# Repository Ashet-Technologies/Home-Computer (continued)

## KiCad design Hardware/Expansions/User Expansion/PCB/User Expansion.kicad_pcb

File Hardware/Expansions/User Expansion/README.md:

# User Expansion

This expansion card allows one to create their own expansions.

It contains all necessary parts like the connector and the metadata EEPROM, but apart from that, it just exposes all signals onto a perfboard.

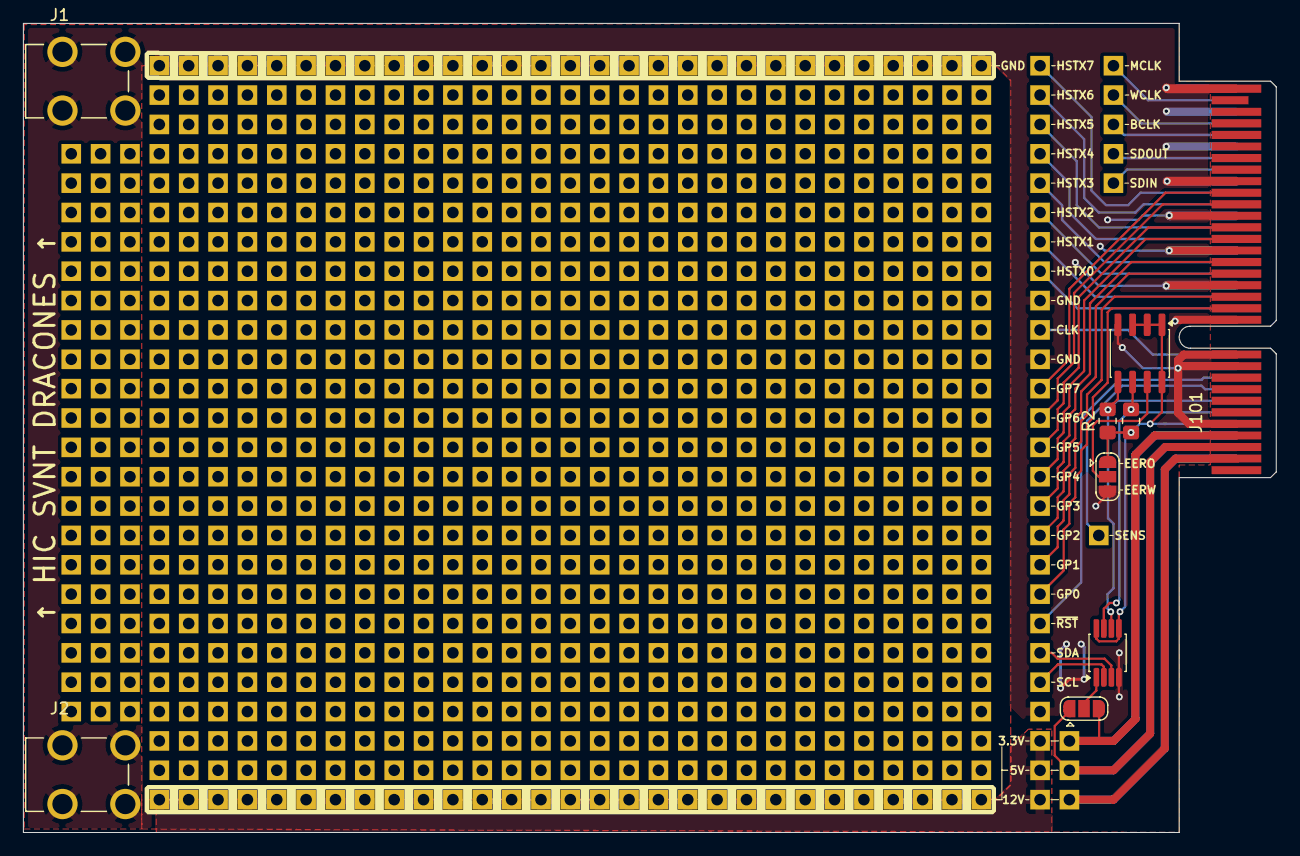
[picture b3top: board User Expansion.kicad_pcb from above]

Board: 2 copper layers, 108.4 x 70.0 mm, 102 parts (0 on the bottom side), 36 nets.

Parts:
J1, J2: 7774; KEYSTONE_7774
J101: BUS_PCIexpress_x4
JP101, JP102: WP; SolderJumper-3_P1.3mm_Open_RoundedPad1.0x1.5mm
R1, R2: 10K; R_0805_2012Metric_Pad1.20x1.40mm_HandSolder
TP101, TP104, TP105, TP106, TP107, TP108, TP109, TP110, TP111, TP112, TP113, TP114, TP115, TP116, TP117, TP118, TP119, TP120, TP121, TP122, TP123, TP124, TP125, TP126, TP127, TP132, TP133, TP135, TP136, TP137, TP138, TP139, TP140, TP141, TP142: Perfboard_Pad_P2.54mm
TP1301, TP1302, TP1303, TP1304, TP1305, TP1306, TP1307, TP1308, TP1309, TP1310, TP1311, TP1312, TP1313, TP1314, TP1315, TP1316, TP1317, TP1318, TP1319, TP1320, TP1321, TP1322, TP1323, TP1324, TP1325, TP1326, TP1327, TP1328, TP1329, TP1401, TP1402, TP1403, TP1404, TP1405, TP1406, TP1407, TP1408, TP1409, TP1410, TP1411, TP1412, TP1413, TP1414, TP1415, TP1416, TP1417, TP1418, TP1419, TP1420, TP1421, TP1422, TP1423, TP1425, TP1426, TP1427, TP1429, TP1430, TP1431: -; Perfboard_Pad_P2.54mm
U1: 24LC256; SOIC-8_3.9x4.9mm_P1.27mm
U2: TCA9517ADGKR; VSSOP-8_3x3mm_P0.65mm

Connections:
+3.3VP: J101.A5 (+3V3_ID), JP101.1 (A), R1.1, R2.1, U1.1 (A0), U1.2 (A1), U1.3 (A2), U1.8 (VCC), U2.5 (EN), U2.8 (VCC_{B})
+3V3: J101.A4 (+3V3), J101.B4 (+3V3), JP102.3 (B), TP141.1 (1_1)
+5V: J101.A3 (+5V), J101.B3 (+5V), JP102.1 (A), TP139.1 (1_1)
+12V: J101.A2 (+12V), J101.B2 (+12V), TP140.1 (1_1)
/CLK: J101.A11 (CLK), TP106.1 (1_1)
/Connected Row1/COM: TP135.1 (1_1), TP137.1 (1_1), TP138.1 (1_1), TP1401.1 (1_1), TP1402.1 (1_1), TP1403.1 (1_1), TP1404.1 (1_1), TP1405.1 (1_1), TP1406.1 (1_1), TP1407.1 (1_1), TP1408.1 (1_1), TP1409.1 (1_1), TP1410.1 (1_1), TP1411.1 (1_1), TP1412.1 (1_1), TP1413.1 (1_1), TP1414.1 (1_1), TP1415.1 (1_1), TP1416.1 (1_1), TP1417.1 (1_1), TP1418.1 (1_1), TP1419.1 (1_1), TP1420.1 (1_1), TP1421.1 (1_1), TP1422.1 (1_1), TP1423.1 (1_1), TP1425.1 (1_1), TP1426.1 (1_1), TP1427.1 (1_1), TP1429.1 (1_1), TP1430.1 (1_1), TP1431.1 (1_1)
/GP0: J101.B13 (GP0), TP115.1 (1_1)
/GP1: J101.B14 (GP1), TP116.1 (1_1)
/GP2: J101.B16 (GP2), TP117.1 (1_1)
/GP3: J101.B17 (GP3), TP118.1 (1_1)
/GP4: J101.B19 (GP4), TP119.1 (1_1)
/GP5: J101.B20 (GP5), TP120.1 (1_1)
/GP6: J101.B22 (GP6), TP121.1 (1_1)
/GP7: J101.B23 (GP7), TP122.1 (1_1)
/HSTX0: J101.A13 (HSTX0), TP107.1 (1_1)
/HSTX1: J101.A14 (HSTX1), TP108.1 (1_1)
/HSTX2: J101.A16 (HSTX2), TP109.1 (1_1)
/HSTX3: J101.A17 (HSTX3), TP110.1 (1_1)
/HSTX4: J101.A19 (HSTX4), TP111.1 (1_1)
/HSTX5: J101.A20 (HSTX5), TP112.1 (1_1)
/HSTX6: J101.A22 (HSTX6), TP113.1 (1_1)
/HSTX7: J101.A23 (HSTX7), TP114.1 (1_1)
/I2S_BCLK: J101.A28 (I2S_BCLK), TP125.1 (1_1)
/I2S_MCLK: J101.A31 (I2S_MCLK), TP127.1 (1_1)
/I2S_SDIN: J101.A25 (I2S_SDIN), TP123.1 (1_1)
/I2S_SDOUT: J101.A26 (I2S_SDOUT), TP124.1 (1_1)
/I2S_WCLK: J101.A29 (I2S_WCLK), TP126.1 (1_1)
/MOD_SENS: J101.A8 (+3V3_10K), TP104.1 (1_1)
/SCL: TP132.1 (1_1), U2.2 (SCL_{A})
/SCL_{ID}: J101.A6 (I2C_SCL), R1.2, U1.6 (SCL), U2.7 (SCL_{B})
/SDA: TP142.1 (1_1), U2.3 (SDA_{A})
/SDA_{ID}: J101.A7 (I2C_SDA), R2.2, U1.5 (SDA), U2.6 (SDA_{B})
/~RESET: J101.A9 (~RESET), TP105.1 (1_1)
GND: J1.1_1, J1.1_2, J1.1_3, J1.1_4, J2.1_1, J2.1_2, J2.1_3, J2.1_4, J101.A10 (GND), J101.A12 (GND), J101.A15 (GND), J101.A18 (GND), J101.A21 (GND), J101.A24 (GND), J101.A27 (GND), J101.A30 (GND), J101.A32 (GND), J101.B5 (GND), J101.B10 (~PRESENT), J101.B11 (GND), J101.B12 (GND), J101.B15 (GND), J101.B18 (GND), J101.B21 (GND), J101.B24 (GND), J101.B32 (GND), JP101.3 (B), TP101.1 (1_1), TP133.1 (1_1), TP136.1 (1_1), TP1301.1 (1_1), TP1302.1 (1_1), TP1303.1 (1_1), TP1304.1 (1_1), TP1305.1 (1_1), TP1306.1 (1_1), TP1307.1 (1_1), TP1308.1 (1_1), TP1309.1 (1_1), TP1310.1 (1_1), TP1311.1 (1_1), TP1312.1 (1_1), TP1313.1 (1_1), TP1314.1 (1_1), TP1315.1 (1_1), TP1316.1 (1_1), TP1317.1 (1_1), TP1318.1 (1_1), TP1319.1 (1_1), TP1320.1 (1_1), TP1321.1 (1_1), TP1322.1 (1_1), TP1323.1 (1_1), TP1324.1 (1_1), TP1325.1 (1_1), TP1326.1 (1_1), TP1327.1 (1_1), TP1328.1 (1_1), TP1329.1 (1_1), U1.4 (GND), U2.4 (GND)
unnamed: JP101.2 (C), U1.7 (WP)
unnamed: JP102.2 (C), U2.1 (VCC_{A})

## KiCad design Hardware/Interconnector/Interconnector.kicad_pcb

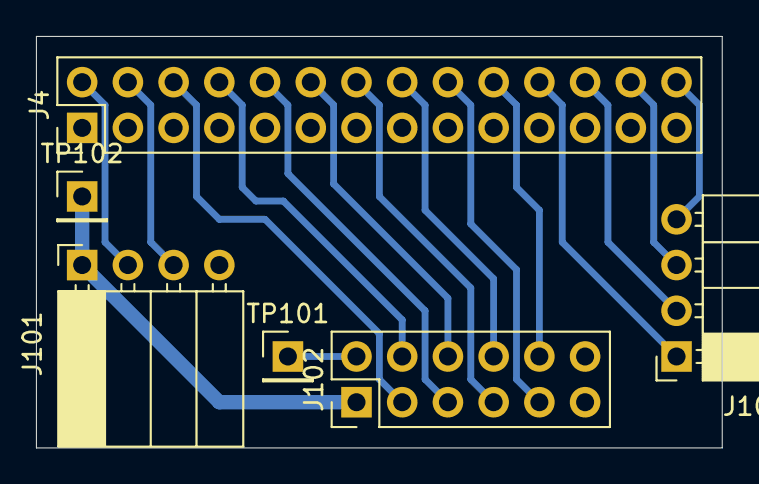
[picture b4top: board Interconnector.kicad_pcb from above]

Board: 2 copper layers, 38.1 x 22.9 mm, 6 parts (0 on the bottom side), 17 nets.

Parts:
J4: Conn_Center; PinHeader_2x14_P2.54mm_Vertical
J101, J103: Conn_01x04; PinSocket_1x04_P2.54mm_Horizontal
J102: Conn_02x06_Odd_Even; PinHeader_2x06_P2.54mm_Vertical
TP101, TP102: TestPoint; PinHeader_1x01_P2.54mm_Vertical

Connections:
+3.3V: J101.1, J102.1, TP102.1
/GPIO22: J4.2, J101.2
/GPIO23: J4.4, J101.3
/GPIO24: J4.6, J102.3
/GPIO25: J4.8, J102.4
/GPIO26: J4.10, J102.5
/GPIO27: J4.12, J102.6
/GPIO28: J4.14, J102.7
/GPIO29: J4.16, J102.8
/GPIO30: J4.18, J102.9
/GPIO31: J4.20, J102.10
/GPIO32: J4.22, J103.1
/GPIO33: J4.24, J103.2
/GPIO34: J4.26, J103.3
/GPIO35: J4.28, J103.4
/~P2_RES: J102.2, TP101.1
GND: J4.1, J4.3, J4.5, J4.7, J4.9, J4.11, J4.13, J4.15, J4.17, J4.19, J4.21, J4.23, J4.25, J4.27, J101.4, J102.11, J102.12

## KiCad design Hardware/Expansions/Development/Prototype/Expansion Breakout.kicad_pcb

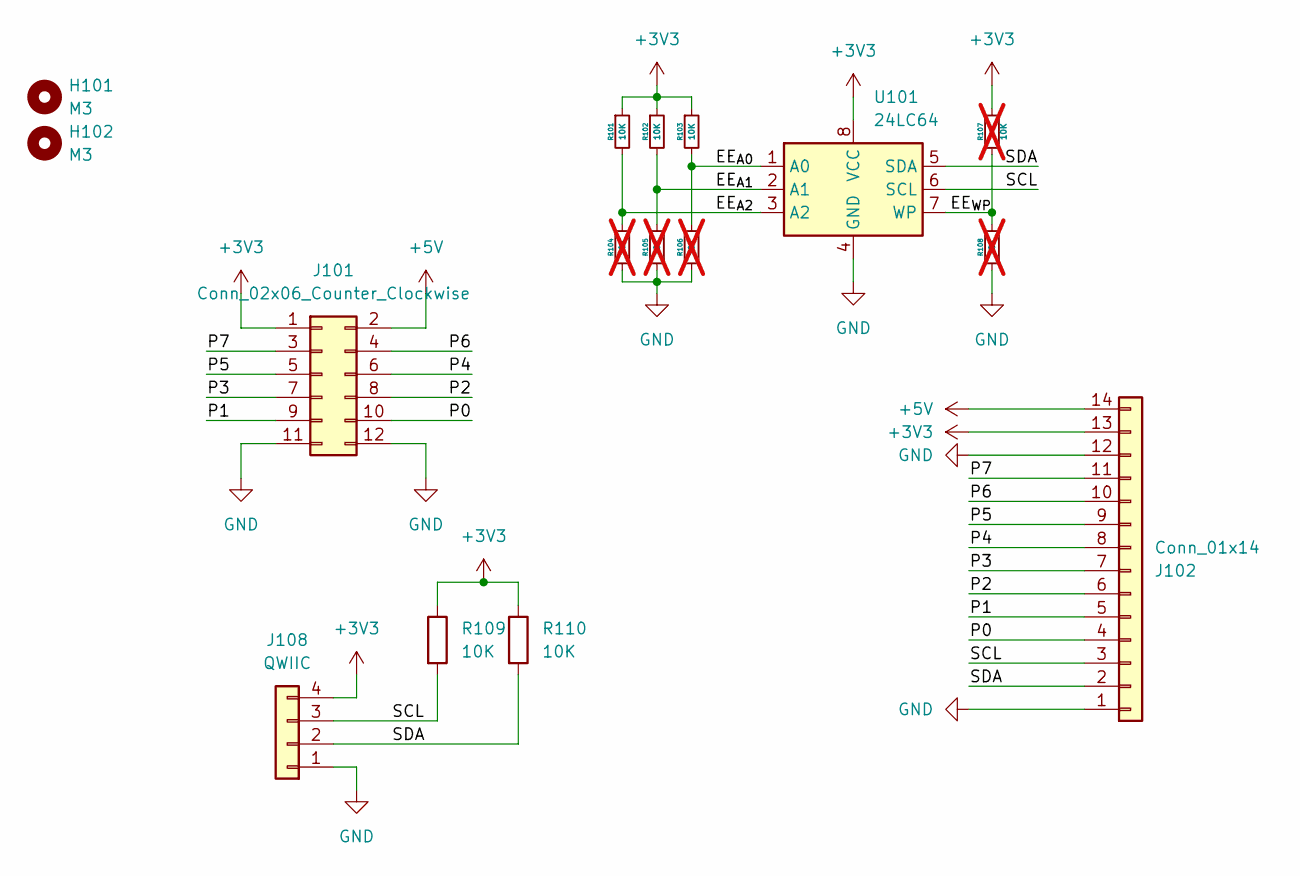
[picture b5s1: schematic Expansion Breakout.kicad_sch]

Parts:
H101, H102: M3; MountingHole_3.2mm_M3_ISO7380
J101: Conn_02x06_Counter_Clockwise; PinHeader_2x06_P2.54mm_Vertical
J102: Conn_01x14; PinSocket_1x14_P2.54mm_Horizontal
J108: QWIIC; PinSocket_1x04_P2.54mm_Horizontal
R101, R102, R103: 10K; R_0603_1608Metric_Pad0.98x0.95mm_HandSolder
R104, R105, R106, R107, R108: 10K; R_0603_1608Metric_Pad0.98x0.95mm_HandSolder; not fitted
R109, R110: 10K; R_Axial_DIN0207_L6.3mm_D2.5mm_P10.16mm_Horizontal
U101: 24LC64; DIP-8_W7.62mm_LongPads

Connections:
+3V3: J101.1, J102.13, J108.4, R101.1, R102.1, R103.1, R107.1, R109.1, R110.1, U101.8 (VCC)
+5V: J101.2, J102.14
/EE_{A0}: R103.2, R106.1, U101.1 (A0)
/EE_{A1}: R102.2, R105.1, U101.2 (A1)
/EE_{A2}: R101.2, R104.1, U101.3 (A2)
/EE_{WP}: R107.2, R108.1, U101.7 (WP)
/P0: J101.10, J102.4
/P1: J101.9, J102.5
/P2: J101.8, J102.6
/P3: J101.7, J102.7
/P4: J101.6, J102.8
/P5: J101.5, J102.9
/P6: J101.4, J102.10
/P7: J101.3, J102.11
/SCL: J102.3, J108.3, R109.2, U101.6 (SCL)
/SDA: J102.2, J108.2, R110.2, U101.5 (SDA)
GND: J101.11, J101.12, J102.1, J102.12, J108.1, R104.2, R105.2, R106.2, R108.2, U101.4 (GND)

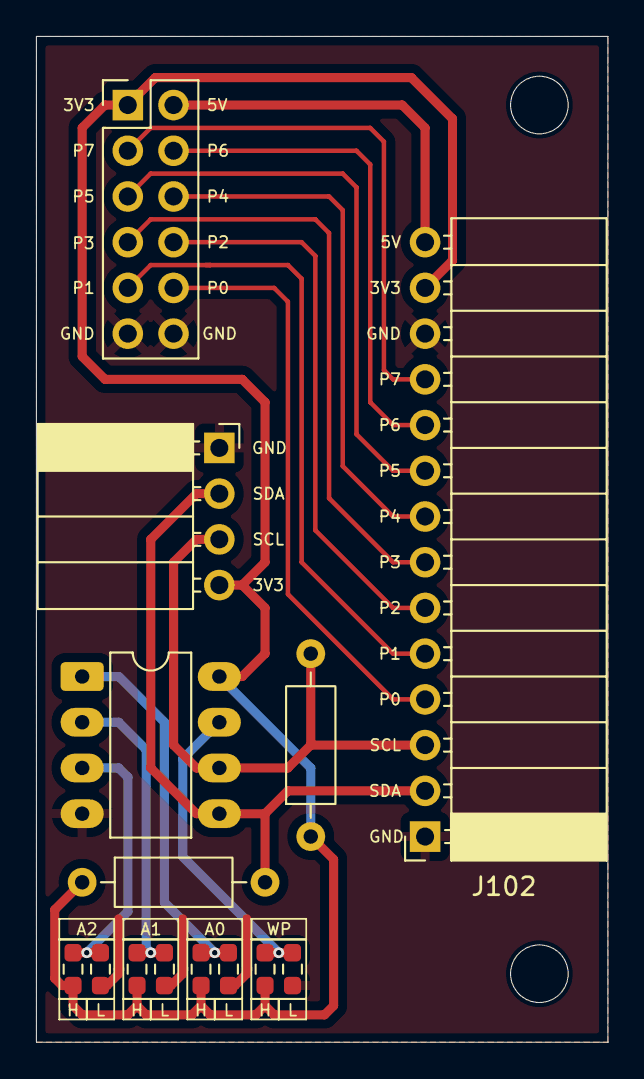
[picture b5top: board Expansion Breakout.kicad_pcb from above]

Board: 2 copper layers, 31.8 x 55.9 mm, 16 parts (0 on the bottom side), 17 nets.

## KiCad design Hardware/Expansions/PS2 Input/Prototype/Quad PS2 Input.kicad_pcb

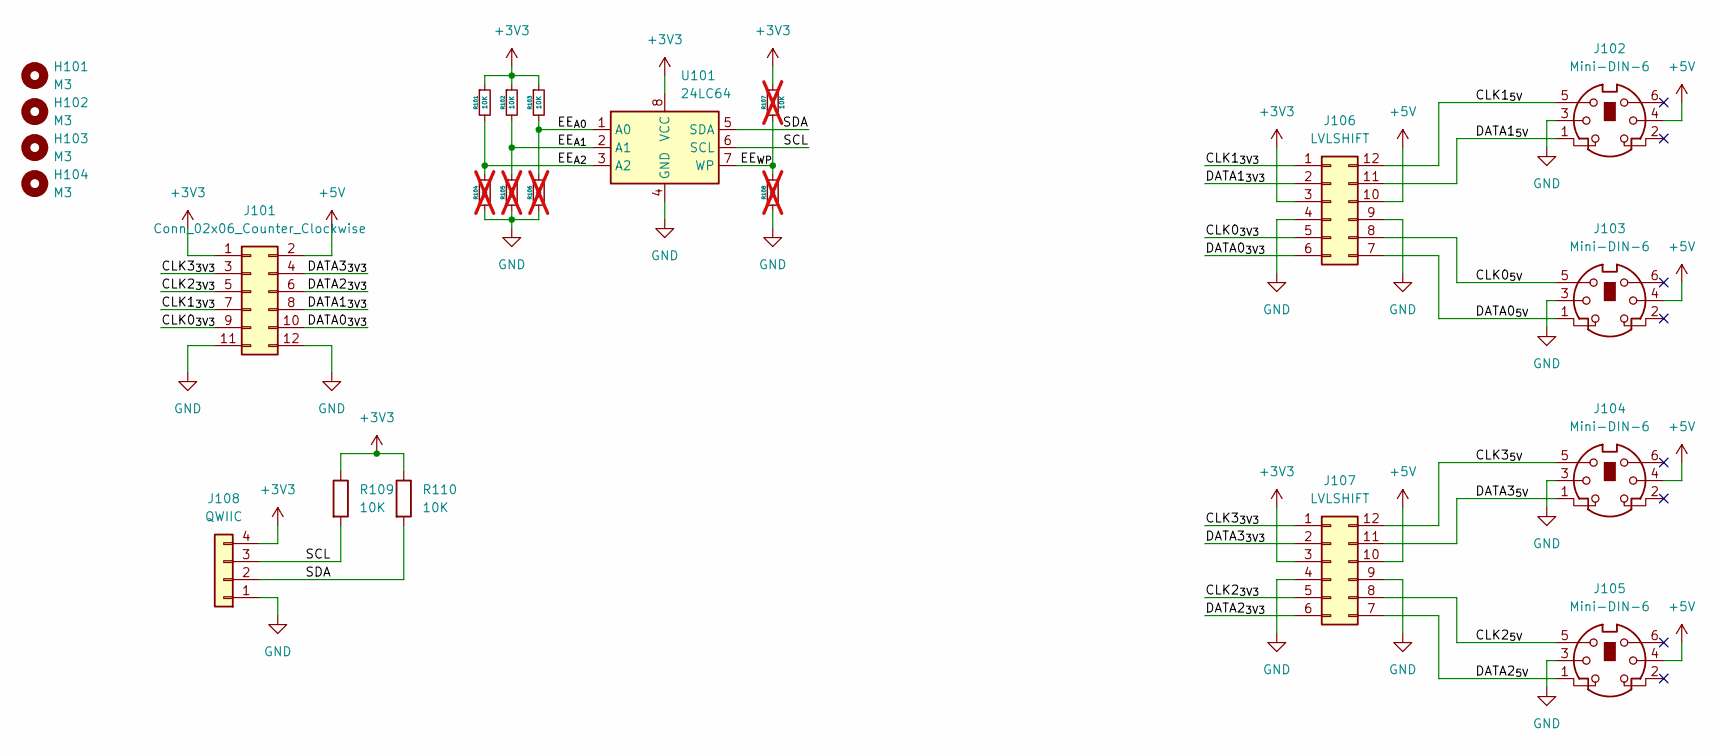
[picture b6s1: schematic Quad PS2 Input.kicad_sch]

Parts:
H101, H102, H103, H104: M3; MountingHole_3.2mm_M3_ISO7380
J101: Conn_02x06_Counter_Clockwise; PinHeader_2x06_P2.54mm_Vertical
J102, J103, J104, J105: Mini-DIN-6; J_Mini-DIN-6
J106, J107: LVLSHIFT; DIP-12_W10.16mm
J108: QWIIC; PinSocket_1x04_P2.54mm_Horizontal
R101, R102, R103: 10K; R_0603_1608Metric_Pad0.98x0.95mm_HandSolder
R104, R105, R106, R107, R108: 10K; R_0603_1608Metric_Pad0.98x0.95mm_HandSolder; not fitted
R109, R110: 10K; R_Axial_DIN0207_L6.3mm_D2.5mm_P10.16mm_Horizontal
U101: 24LC64; DIP-8_W7.62mm_LongPads

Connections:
+3V3: J101.1, J106.3, J107.3, J108.4, R101.1, R102.1, R103.1, R107.1, R109.1, R110.1, U101.8 (VCC)
+5V: J101.2, J102.4, J103.4, J104.4, J105.4, J106.10, J107.10
/CLK0_{3V3}: J101.9, J106.5
/CLK0_{5V}: J103.5, J106.8
/CLK1_{3V3}: J101.7, J106.1
/CLK1_{5V}: J102.5, J106.12
/CLK2_{3V3}: J101.5, J107.5
/CLK2_{5V}: J105.5, J107.8
/CLK3_{3V3}: J101.3, J107.1
/CLK3_{5V}: J104.5, J107.12
/DATA0_{3V3}: J101.10, J106.6
/DATA0_{5V}: J103.1, J106.7
/DATA1_{3V3}: J101.8, J106.2
/DATA1_{5V}: J102.1, J106.11
/DATA2_{3V3}: J101.6, J107.6
/DATA2_{5V}: J105.1, J107.7
/DATA3_{3V3}: J101.4, J107.2
/DATA3_{5V}: J104.1, J107.11
/EE_{A0}: R103.2, R106.1, U101.1 (A0)
/EE_{A1}: R102.2, R105.1, U101.2 (A1)
/EE_{A2}: R101.2, R104.1, U101.3 (A2)
/EE_{WP}: R107.2, R108.1, U101.7 (WP)
/SCL: J108.3, R109.2, U101.6 (SCL)
/SDA: J108.2, R110.2, U101.5 (SDA)
GND: J101.11, J101.12, J102.3, J103.3, J104.3, J105.3, J106.4, J106.9, J107.4, J107.9, J108.1, R104.2, R105.2, R106.2, R108.2, U101.4 (GND)

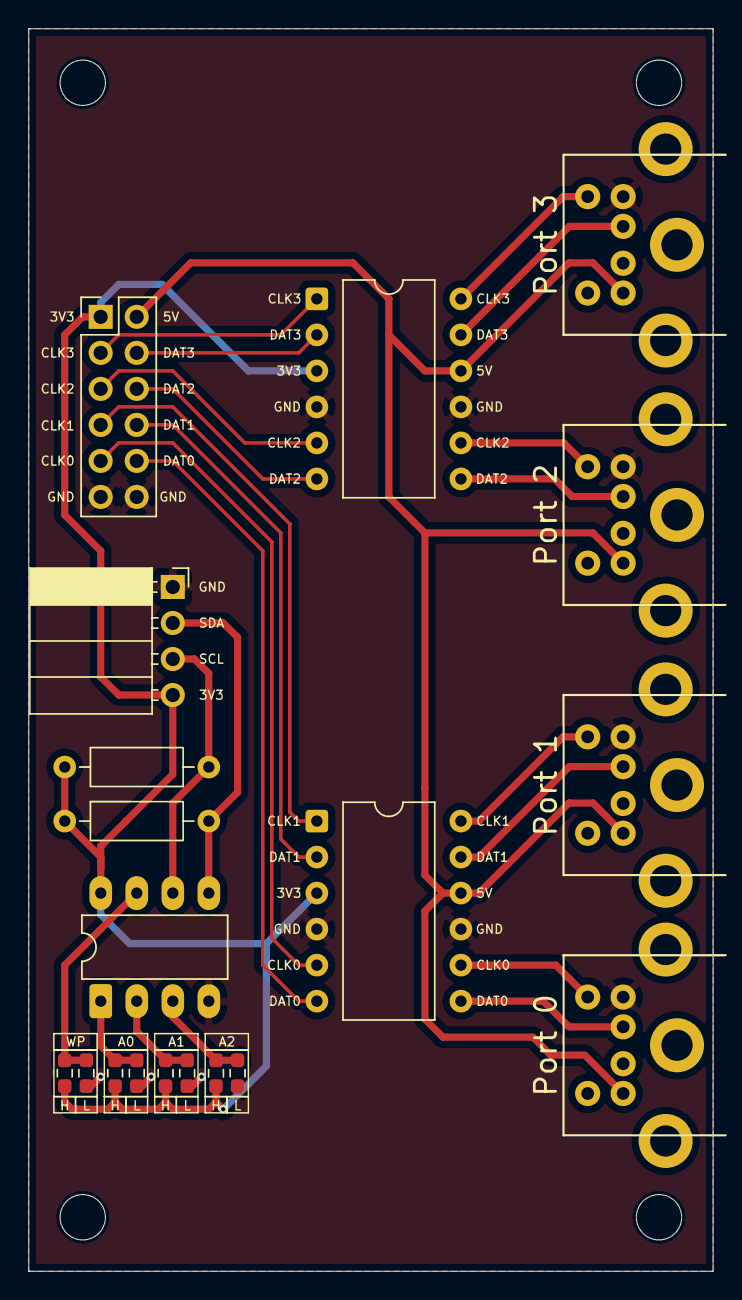
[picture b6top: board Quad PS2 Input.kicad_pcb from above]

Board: 2 copper layers, 48.3 x 87.6 mm, 23 parts (0 on the bottom side), 25 nets.

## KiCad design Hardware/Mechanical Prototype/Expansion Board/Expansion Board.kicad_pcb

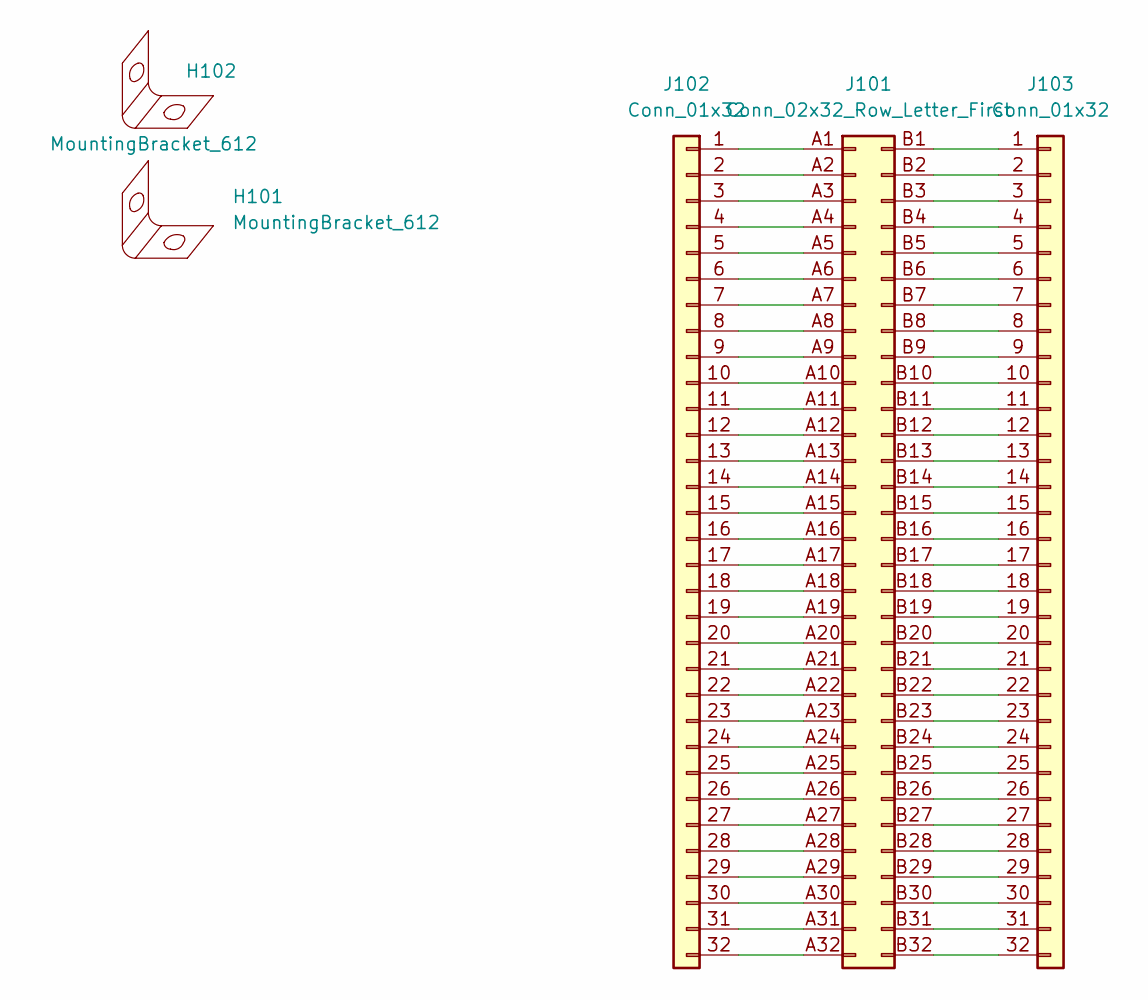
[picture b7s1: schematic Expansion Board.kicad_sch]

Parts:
H101, H102: MountingBracket_612; MountingBracket_612_M3
J101: Conn_02x32_Row_Letter_First; BUS_PCIexpress_x4
J102, J103: Conn_01x32; PinHeader_1x32_P2.54mm_Vertical

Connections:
unnamed: J101.A1, J102.1
unnamed: J101.A2, J102.2
unnamed: J101.A3, J102.3
unnamed: J101.A4, J102.4
unnamed: J101.A5, J102.5
unnamed: J101.A6, J102.6
unnamed: J101.A7, J102.7
unnamed: J101.A8, J102.8
unnamed: J101.A9, J102.9
unnamed: J101.A10, J102.10
unnamed: J101.A11, J102.11
unnamed: J101.A12, J102.12
unnamed: J101.A13, J102.13
unnamed: J101.A14, J102.14
unnamed: J101.A15, J102.15
unnamed: J101.A16, J102.16
unnamed: J101.A17, J102.17
unnamed: J101.A18, J102.18
unnamed: J101.A19, J102.19
unnamed: J101.A20, J102.20
unnamed: J101.A21, J102.21
unnamed: J101.A22, J102.22
unnamed: J101.A23, J102.23
unnamed: J101.A24, J102.24
unnamed: J101.A25, J102.25
unnamed: J101.A26, J102.26
unnamed: J101.A27, J102.27
unnamed: J101.A28, J102.28
unnamed: J101.A29, J102.29
unnamed: J101.A30, J102.30
unnamed: J101.A31, J102.31
unnamed: J101.A32, J102.32
unnamed: J101.B1, J103.1
unnamed: J101.B2, J103.2
unnamed: J101.B3, J103.3
unnamed: J101.B4, J103.4
unnamed: J101.B5, J103.5
unnamed: J101.B6, J103.6
unnamed: J101.B7, J103.7
unnamed: J101.B8, J103.8
unnamed: J101.B9, J103.9
unnamed: J101.B10, J103.10
unnamed: J101.B11, J103.11
unnamed: J101.B12, J103.12
unnamed: J101.B13, J103.13
unnamed: J101.B14, J103.14
unnamed: J101.B15, J103.15
unnamed: J101.B16, J103.16
unnamed: J101.B17, J103.17
unnamed: J101.B18, J103.18
unnamed: J101.B19, J103.19
unnamed: J101.B20, J103.20
unnamed: J101.B21, J103.21
unnamed: J101.B22, J103.22
unnamed: J101.B23, J103.23
unnamed: J101.B24, J103.24
unnamed: J101.B25, J103.25
unnamed: J101.B26, J103.26
unnamed: J101.B27, J103.27
unnamed: J101.B28, J103.28
unnamed: J101.B29, J103.29
unnamed: J101.B30, J103.30
unnamed: J101.B31, J103.31
unnamed: J101.B32, J103.32

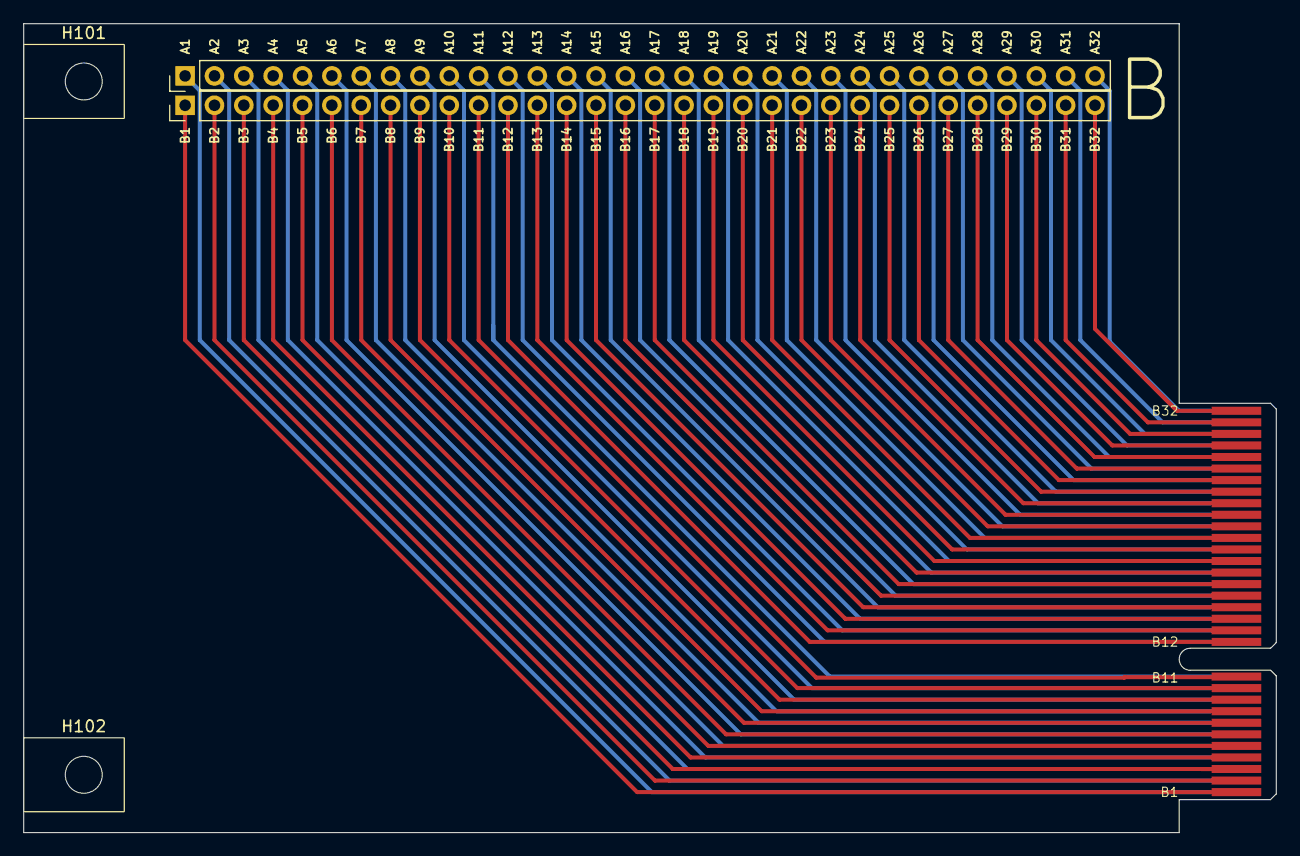
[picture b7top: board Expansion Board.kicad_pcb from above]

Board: 2 copper layers, 108.4 x 70.0 mm, 5 parts (0 on the bottom side), 64 nets.

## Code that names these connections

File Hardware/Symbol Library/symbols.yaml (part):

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      PA2:
        type: logic-inout
        position: R11
      PD0:
        type: logic-inout
        position: R1
      PD1:
        type: logic-inout
        position: R2
      PD2:
        type: logic-inout
        position: R3
      PD3:
        type: logic-inout
        position: R4
      PD4:
        type: logic-inout
        position: R5
      PD5:
        type: logic-inout
        position: R6
      PD6:
        type: logic-inout
        position: R7
      PD7:
        type: logic-inout
        position: R8
      PC0:
        type: logic-inout
        position: L1
      PC1:
        type: logic-inout
        position: L2
      PC2:
        type: logic-inout
        position: L3
      PC3:
        type: logic-inout
        position: L4
      PC4:
        type: logic-inout
        position: L5
      PC5:
        type: logic-inout
        position: L6
      PC6:
        type: logic-inout
        position: L7
      PC7:
        type: logic-inout
        position: L8

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      CH32V003F4P6:
        footprint: ~ # TSSOP20
        pinout:
          1: PD4
          2: PD5
          3: PD6
          4: PD7
          5: PA1
          6: PA2
          7: VSS
          8: PD0
          9: VDD
          10: PC0
          11: PC1
          12: PC2
          13: PC3
          14: PC4
          15: PC5
          16: PC6
          17: PC7
          18: PD1
          19: PD2
          20: PD3
        distributors:
          lcsc:
            url: https://www.lcsc.com/product-detail/C5187096.html
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        footprint: ~ # QFN20
        pinout:
          0: VSS # exposed pad?
          1: PD7
          2: PA1
          3: PA2
          4: VSS
          5: PD0
          6: VDD
          7: PC0
          8: PC1
          9: PC2
          10: PC3
          11: PC4
          12: PC5
          13: PC6
          14: PC7
          15: PD1
          16: PD2
          17: PD3
          18: PD4
          19: PD5
          20: PD6
        distributors:
          lcsc:
            url: https://www.lcsc.com/product-detail/C5299908.html
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      CH32V003A4M6:
        footprint: ~ # SOP16
        pinout:
          1: PC1
          2: PC2
          3: PC3
          4: PC4
          5: PC6
          6: PC7
          7: PD1
          8: PD4
          9: PD5
          10: PD6
          11: PD7
          12: PA1
          13: PA2
          14: VSS
          15: VDD
          16: PC0
        distributors:
          lcsc:
            url: https://www.lcsc.com/product-detail/C5346357.html
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      CH32V003J4M6:
        footprint: ~ # SOP8
        pinout:
          1: PD5 # multi-mapping: PD5, PA1
          2: VSS 
          3: PA2
          4: VDD
          5: PC1
          6: PC2
          7: PC4
          8: PD4 # multi-mapping: PD4, PD5, PD1
        distributors:
          lcsc:
            url: https://www.lcsc.com/product-detail/C5346354.html
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
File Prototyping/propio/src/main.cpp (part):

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};

enum GeneralPurposePort : uint {
  GP_0 = 24,
  GP_1 = 25,
  GP_2 = 35,
  GP_3 = 34,
  GP_4 = 33,
  GP_5 = 32,
  GP_6 = 30,
  GP_7 = 31,
};

struct GeneralIO {
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struct UartDriver : Driver {
  PIO pio = pio0;
  uint sm_tx_id = 0;
  uint pin_tx0 = GP_0;

  void init() override {
    pio_sm_set_enabled(pio, sm_tx_id, false);
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
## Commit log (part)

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2024-08-28 Initial commit: Adds some brain dump
2024-08-28 Updates README.md with features.
2024-08-28 Updates SVG file with background.
2024-09-04 Adds first prototypical mainboard pcb
2024-09-05 Adds datasheets for audio and i2c parts
2024-09-06 Adds more work on the mainboard schematic
2024-09-06 Adds RP2350 Stamp XL and dummy expansion board
2024-09-09 Adds pull-ups and irq controller to expansion subsystem
2024-09-11 More work on the motherboard
2024-10-15 Adds some computations for the GPU timings and bandwith
2024-10-15 Cleans up GPU computations
2024-11-20 Adds case draft concept
2024-12-12 Adds new backplane design using general purpose ports, and propeller. very non-finished concept
2024-12-16 Adds more docs
2024-12-16 Adds more work on the backplane.
2024-12-18 Overhauls README.md a lot.
2024-12-19 Adds some more specification and concepts
2024-12-21 Makes prototyping plan, improves southbridge interface definition
2024-12-21 snapshot before refactor
2024-12-21 Updates Expansion Bay Pinout
2024-12-21 Adds prototyping env
2024-12-28 Updates README.md
2024-12-28 Adds case experiment for creating a renderable case preview
2024-12-28 Adds HDMI experiment, adds turboprop code loader, adds propeller datasheets
2024-12-29 Adds connector models for improved preview
2024-12-29 Adds more models
2024-12-29 Adds nice visuals
2024-12-29 Adds concept art to readme.
2024-12-31 Adds Cody Computer to comparison table
2024-12-31 Adds prototype PSRAM datasheet
2025-01-01 Adds a 'use case' section to the README
2025-01-03 Adds RaspberryPi size reference and slot variant.
2025-01-03 Adds really nice case update, found fitting case.
2025-01-03 updates case screenshot.
2025-01-04 Adds working PSRAM prototype
2025-01-04 Builds flexspin via build.zig
2025-01-04 Adds blinky example.
2025-01-05 Adds turboprop improvements, adds serial echo demo
2025-01-06 starts to implement propio southbridge interconnect prototype
2025-01-08 Adds tooling to compute device prices for batch sizes
2025-01-08 Adds more documentation
2025-01-08 Starts to implement propeller propio code
2025-01-08 Implements nibble based transaction between mainboard and southbridge
2025-01-08 Some fine tunings on the code
2025-01-08 Adds User Expansion PCB
2025-01-10 Improves turboprop cli
2025-01-10 Adds draft of propan assembler
2025-01-13 Adds new project goal
2025-01-14 Implements interrupt based propio receiver
2025-01-14 Adds PIO based UART for high-speed UART sending, adjusts propeller to receive data
2025-01-14 Improves propio-client
2025-01-14 Adds improved propio control software
2025-01-14 Adds Propan example file
2025-01-14 Adds more southbridge architecture.
2025-01-15 Changes IF_Z to if(Z) prefix in Propan
2025-01-19 Propio improved packet decoding routine, propio packet encoding on RP2350, adds prototype for VBS generation
2025-01-22 Drops propan examples and moves them to different repo
2025-01-22 Fixes typo in list of expansion boards.
2025-01-22 Fixes typos inside README.md
2025-01-22 Starts work on real case design
2025-01-23 Creates a 3D model and rendering of the fully assembled case.
2025-01-23 Adds CI workflow for CAD files.
2025-01-24 Continues work on User Expansion design, adds CI for exports, ERC and DRC
2025-01-24 Improves rendering with 3D export of User Expansion Card, updates ERC workflow
2025-01-24 Fixes CI scripts.
2025-01-24 Adds 'topless' rendering mode where the case is opened.
2025-01-26 Improves Backplane Schematic a lot
2025-03-07 Deletes the prototyping code and moves it to its own repository
2025-03-07 Starts designing the mechanical prototype parts, which validate that all of the mechanical design works. They also allow electric prototyping, but only by breaking out all connectors
2025-03-07 First full draft of mechanical backplane and expansion board design
2025-03-08 2025-03-08: Mechanical Prototype, Order #1
2025-04-04 Adds slider design for PCB holders
2025-06-25 Improves the PCB slider by adding a tiny chamfer and widening at the ends, so insertion of the PCB is easier. Also increased the margins as the pcb fit pretty tight.
2025-09-11 Starts to implement expansion card code
2025-09-12 Improves justfile a tad
2025-09-14 Adds two prototype designs for expansion cards. Adjusts expansion spec a little.
2025-09-16 Adds tooling to generate EEPROMs from a central registry.
2025-09-28 Some work on the backplane schematics: Improves module locality
2025-10-02 Starts to implement a tool to generate symbols for KiCAD from a generic description.
2025-10-21 Fixes PS/2 input code for new prototype PCB, adds program.py to flash EEPROM
2025-10-23 Fixes PS/2 Input expansion code and enables it to host all 4 ports at once.
2025-11-20 Cleans up the backplane schematic and improves on features a lot.
2025-11-22 Cleans up schematic, adds clean RESET gating
2025-11-25 Adds CERN-OHL-P licence
    Time to make "permissive licence" actually a thing.
2025-11-26 Updates backplane: Improves voltage measurement dividers, replaces DS1307+ RTC with a much cheaper one, replaces 8 MHz global clock with 48 MHz global clock
2025-11-27 Upgrades power-on reset system to be close to bullet-proof by having a power-good coupled mono flop that continues holding reset after PG goes high for some time
2025-12-04 Add workflow_dispatch trigger to exports.yml
2025-12-04 Add backplane schematic generation to justfile
2025-12-17 Some cleanups of Backplane schematic: Adds DigiKey part numbers, removes unnecessary properties, marks test points as excluded from BOM
2025-12-17 Refactors clock system to use AND gates for clock tree spanning and gating.
2025-12-17 Adds missing datasheet links into schematic
2025-12-17 Cleans up repository.
2025-12-17 Adds missing part datasheets
2025-12-22 Adjusts to review comments
2025-12-22 Adds script to compute price for digikey
2026-01-27 Starts refactoring Backplane to use NL17SZS11-D instead of 4-port AND
2026-02-14 Cleans up Backplane schematic even more. Less parts in the BOM, less mistakes!
2026-02-14 Cleans up power connector.
2026-02-14 Finally renames all modules from MOD1…7 into MOD0…6
2026-02-14 Cleans up schematic even more, consolidates 270 and 100 Ohm resistors into the 560 ohm resistor, as they were only used as series resistors for the mosfets and LED current limiters
2026-02-14 More BOM consolidation
2026-02-16 Dumps all parts onto bcakplane layout.
2026-03-24 Upgrades schematic files to KiCAD 10.0
2026-03-28 Deletes legacy mainboard schematic, adds README.md for Mainboard with concepts and ideas to implement
2026-05-09 Further backplane PCB cleanup.
2026-05-09 Backplane: Fixes missing footprints/parts, starts to work on the layout seriously.
